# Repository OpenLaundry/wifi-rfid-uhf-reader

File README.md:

# RFID UHF READER

# CURRENTLY WAITING PCB

### UHF rfid reader with bluetooth/WIFI/HID

- [ ] Add battery
- [x] ESP32
- [x] VM-5GA

## NEW VERSION ON KICAD

### USING

### SCHEMATIC VIEW

### PCB VIEW

### 3D VIEW

## OLD VERSION ON FUSION360

### SCHEMATIC VIEW

### PCB VIEW

### 3D VIEW

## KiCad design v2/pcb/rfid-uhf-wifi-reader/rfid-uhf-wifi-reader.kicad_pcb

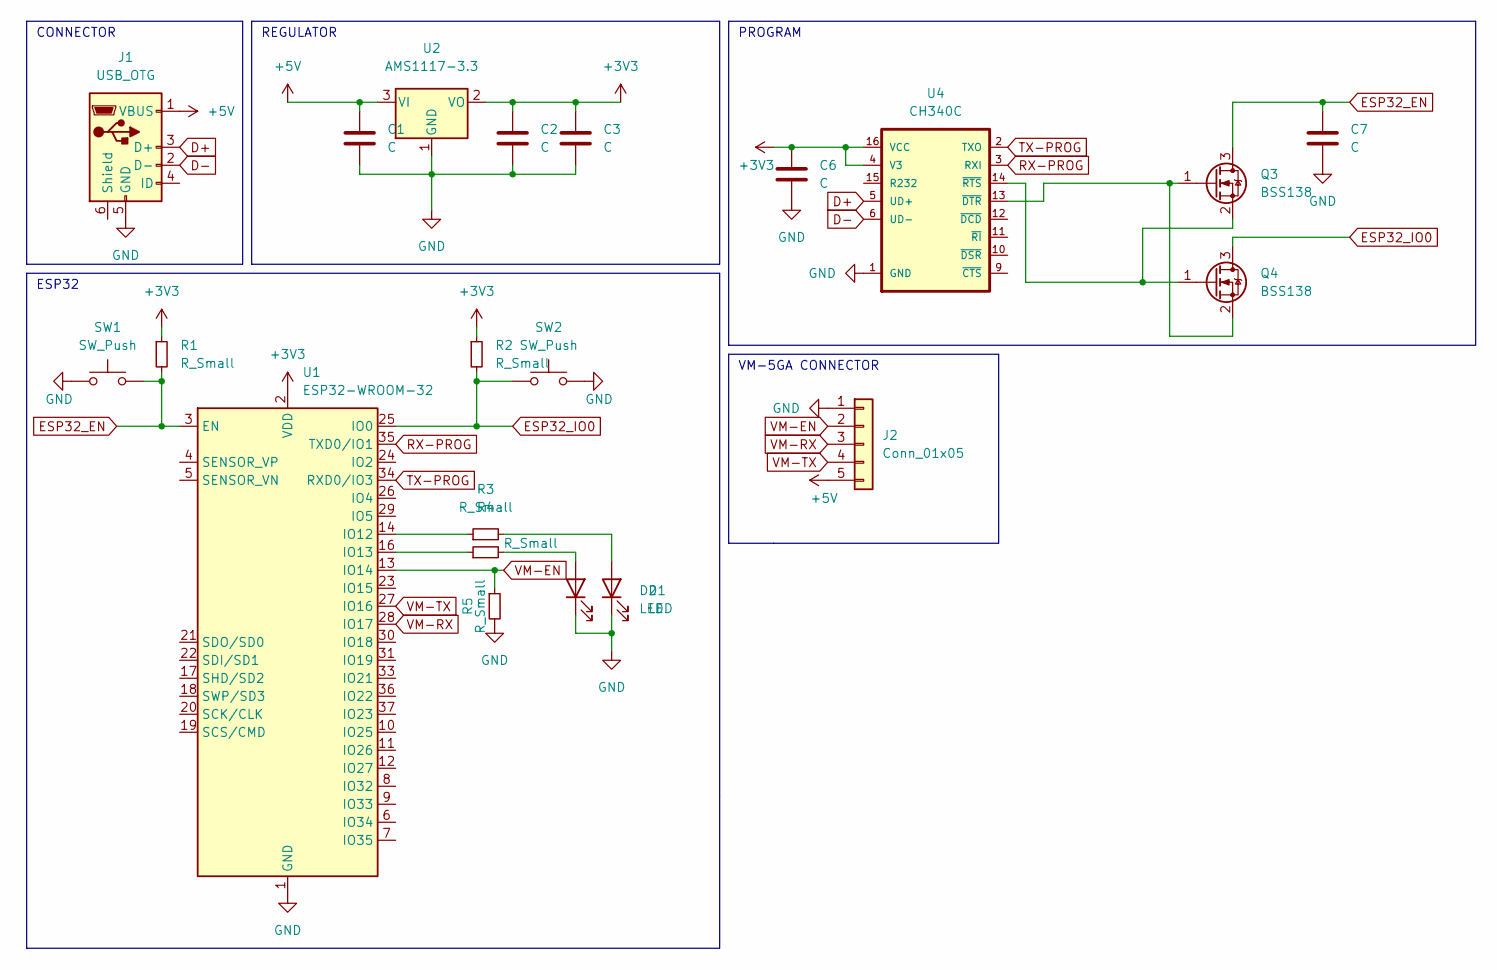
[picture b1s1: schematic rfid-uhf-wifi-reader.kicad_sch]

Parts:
C1, C2, C3, C6, C7: C; C_0603_1608Metric
D1, D2: LED; LED_0603_1608Metric
J1: USB_OTG; USB_Micro-B_Amphenol_10118194_Horizontal
J2: Conn_01x05; PinHeader_1x05_P2.54mm_Vertical
Q3, Q4: BSS138; SOT-23
R1, R2, R3, R4, R5: R_Small; R_0603_1608Metric
SW1, SW2: SW_Push; SW_SPST_FSMSM
U1: ESP32-WROOM-32
U2: AMS1117-3.3; SOT-223-3_TabPin2
U4: CH340C; SO016

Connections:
+3V3: C2.1, C3.1, C6.1, R1.1, R2.1, U1.2 (VDD), U2.2 (VO), U4.4 (V3), U4.16 (VCC)
+5V: C1.1, J1.1 (VBUS), J2.5, U2.3 (VI)
D+: J1.3 (D+), U4.5 (UD+)
D-: J1.2 (D-), U4.6 (UD-)
ESP32_EN: C7.1, Q3.3 (D), R1.2, SW1.2, U1.3 (EN)
ESP32_IO0: Q4.3 (D), R2.2, SW2.1, U1.25 (IO0)
GND: C1.2, C2.2, C3.2, C6.2, C7.2, D1.1 (K), D2.1 (K), J1.5 (GND), J2.1, R5.2, SW1.1, SW2.2, U1.1 (GND), U1.15 (GND), U1.38 (GND), U1.39 (GND), U2.1 (GND), U4.1 (GND)
unnamed: D1.2 (A), R4.2
unnamed: D2.2 (A), R3.2
unnamed: Q3.1 (G), Q4.2 (S), U4.13 (~DTR)
unnamed: Q3.2 (S), Q4.1 (G), U4.14 (~RTS)
unnamed: R3.1, U1.14 (IO12)
unnamed: R4.1, U1.16 (IO13)
RX-PROG: U1.35 (TXD0/IO1), U4.3 (RXI)
TX-PROG: U1.34 (RXD0/IO3), U4.2 (TXO)
VM-EN: J2.2, R5.1, U1.13 (IO14)
VM-RX: J2.3, U1.28 (IO17)
VM-TX: J2.4, U1.27 (IO16)

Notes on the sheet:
VM-5GA CONNECTOR
REGULATOR
ESP32
PROGRAM
CONNECTOR

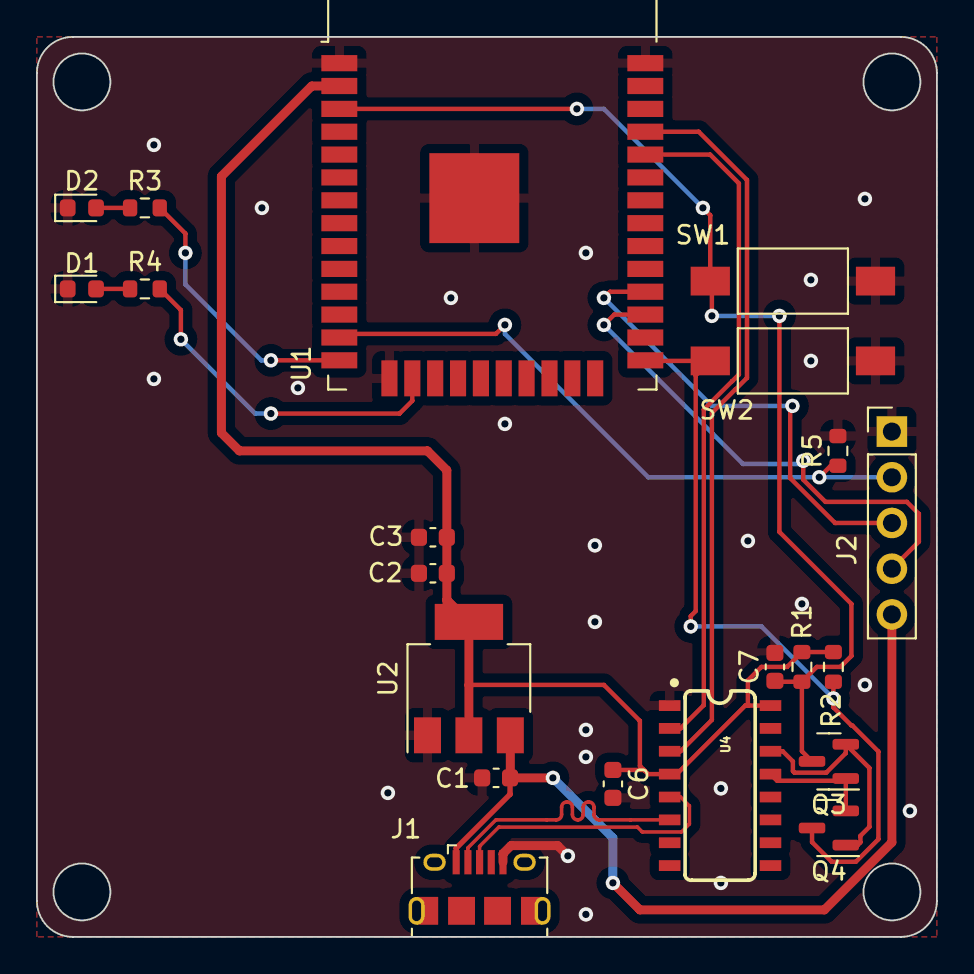
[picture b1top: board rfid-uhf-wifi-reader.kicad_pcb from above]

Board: 2 copper layers, 50.0 x 50.0 mm, 21 parts (0 on the bottom side), 18 nets.

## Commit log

2023-06-28 add pcb project
2023-06-28 add esp32 + usb c
2023-06-28 add ch340
2023-06-28 add en + prod esp32
2023-06-28 add regulator
2023-06-28 add datasheet
2023-06-28 add shematic
2023-06-28 add pcb
2023-06-28 edit project
2023-07-01 place components
2023-07-03 update components
2023-07-04 add leds
2023-07-04 add rfid connector
2023-07-04 add text
2023-07-04 add screenshot
2023-07-04 vm-5ga dev datasheet
2023-07-04 add module screen
2023-07-04 add readme
2023-07-04 add default roject
2023-07-04 add gitignore
2023-07-04 connect to wifi
2023-07-19 move file
2023-07-19 kicad add
2023-07-19 up readme
2023-10-05 fix usb data inverted
2023-10-05 moved project
2023-10-05 fix readme title
2023-10-05 to old
2023-11-10 change ch340
2023-11-10 update ch340c
2023-11-10 finish wiring
2024-06-21 add real pictures
2024-06-22 code first commit
2024-06-22 first commit esp
2024-06-23 remove files
2024-06-23 just blink
2024-06-23 add checksum + cmd send + uart init
